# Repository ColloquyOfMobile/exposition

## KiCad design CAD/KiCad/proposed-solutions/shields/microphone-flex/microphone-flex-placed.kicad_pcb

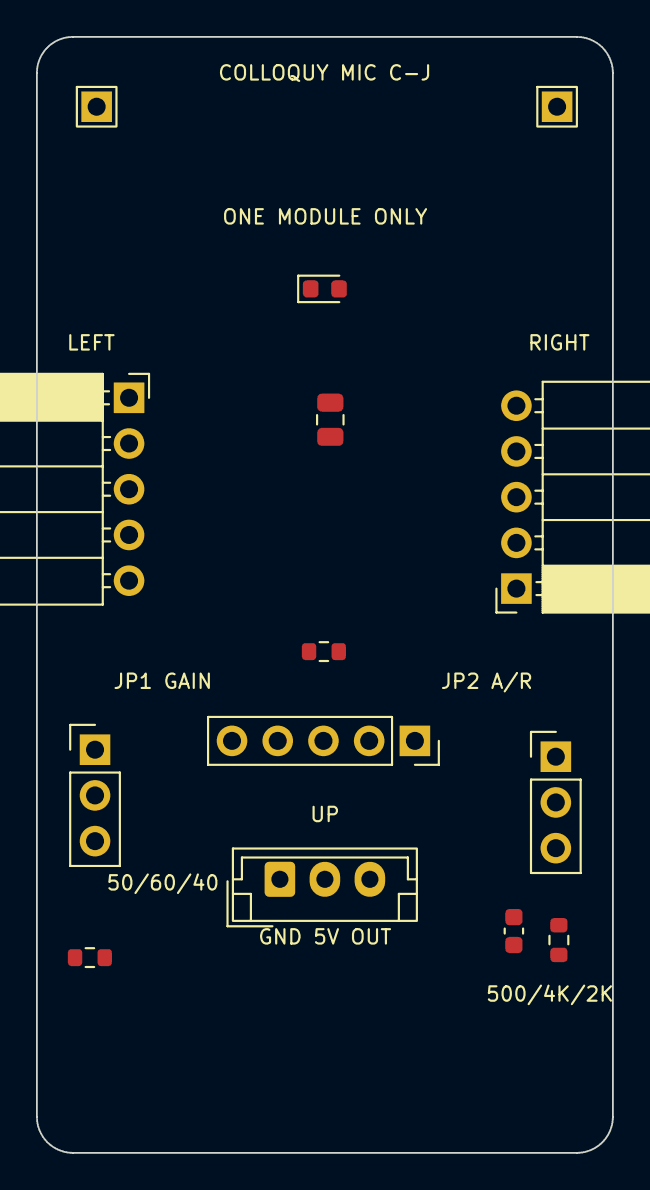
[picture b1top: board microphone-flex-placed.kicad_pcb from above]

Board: 2 copper layers, 32.0 x 62.0 mm, 16 parts (0 on the bottom side), 8 nets, no tracks yet.

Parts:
C6: 100nF; C_0603_1608Metric
C7: 22uF X5R 10V; C_0805_2012Metric
D1: GREEN LED; LED_0603_1608Metric
H1, H2: M5 SLOT 12x5.5 / TRANSVERSE; Flex_M5_Slot12x5.5_Keepout
J1: GND / +5V / OUT; JST_EH_B3B-EH-A_1x03_P2.50mm_Vertical
J2: LEFT / DOWNWARD MODULE; Flex_Socket_Side
J3: RIGHT / DOWNWARD MODULE; Flex_Socket_Side
JP1: GAIN SELECT / HEADER + SHUNT; Flex_Gain_Selector
JP2: AR SELECT / HEADER + SHUNT; Flex_AR_Selector
M1: UP / ONE MODULE ONLY; Flex_Socket_Up
R4: 33R; R_0603_1608Metric
R5: 470R; R_0603_1608Metric
R6: 2K2; R_0603_1608Metric
TP1: MICOUT; TestPin_1x01_P2.54mm
TP2: GND; TestPin_1x01_P2.54mm

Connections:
+5V: J1.2, R4.1, R6.1
AR: J2.5, J3.5, JP2.2, M1.5
GAIN: J2.3, J3.3, JP1.2, M1.3
GND: C6.2, C7.2, D1.1, J1.1, J2.1, J3.1, JP1.1, JP2.1, M1.1, TP2.1
MICOUT: J2.4, J3.4, M1.4, R5.1, TP1.1
OUT: J1.3, R5.2
VDD: C6.1, C7.1, J2.2, J3.2, JP1.3, JP2.3, M1.2, R4.2
led/D1: D1.2, R6.2

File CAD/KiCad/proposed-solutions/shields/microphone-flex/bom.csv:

Reference,Value,Footprint,MPN,Assembly
M1,UP / ONE MODULE ONLY,Shields:Flex_Socket_Up,Existing MAX9814 module + 1x05 2.54mm female socket,fit
R4,33R,Shields:R_0603_1608Metric,,fit
C7,22uF X5R 10V,Shields:C_0805_2012Metric,,fit
C6,100nF,Shields:C_0603_1608Metric,,fit
R6,2K2,Shields:R_0603_1608Metric,,fit
D1,GREEN LED,Shields:LED_0603_1608Metric,,fit
R5,470R,Shields:R_0603_1608Metric,,fit
J1,GND / +5V / OUT,Shields:JST_EH_B3B-EH-A_1x03_P2.50mm_Vertical,B3B-EH-A,fit
TP1,MICOUT,Shields:TestPin_1x01_P2.54mm,,fit
TP2,GND,Shields:TestPin_1x01_P2.54mm,,fit
JP1,GAIN SELECT / HEADER + SHUNT,Shields:Flex_Gain_Selector,Gold plated 1x03 2.54mm vertical header + removable 1x02 shunt,fit
JP2,AR SELECT / HEADER + SHUNT,Shields:Flex_AR_Selector,Gold plated 1x03 2.54mm vertical header + removable 1x02 shunt,fit
J2,LEFT / DOWNWARD MODULE,Shields:Flex_Socket_Left_Overhang,1x05 P2.54mm horizontal female socket; verify purchased dimensions,fit
J3,RIGHT / DOWNWARD MODULE,Shields:Flex_Socket_Right_Overhang,1x05 P2.54mm horizontal female socket; verify purchased dimensions,fit

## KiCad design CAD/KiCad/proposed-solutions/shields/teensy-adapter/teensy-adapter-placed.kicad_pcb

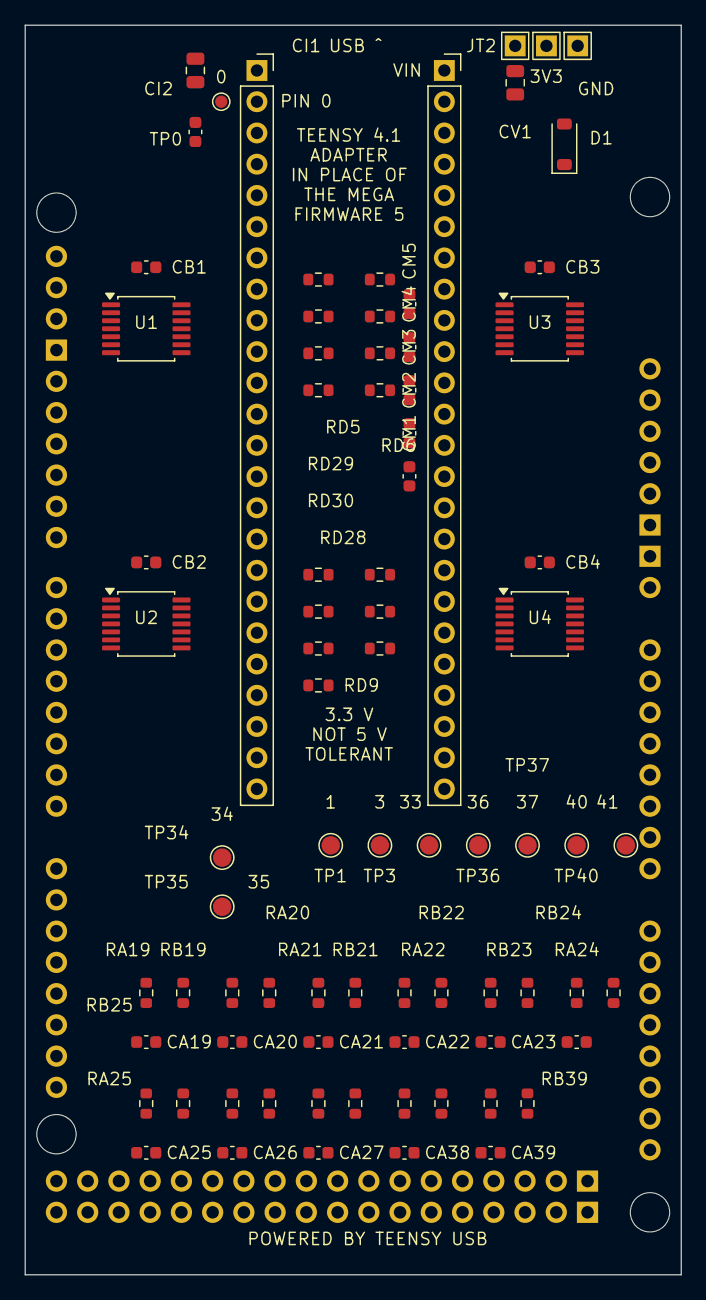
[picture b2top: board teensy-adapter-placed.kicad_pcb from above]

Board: 4 copper layers, 53.3 x 101.6 mm, 85 parts (1 on the bottom side), 71 nets, no tracks yet.

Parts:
CA19, CA20, CA21, CA22, CA23, CA24, CA25, CA26, CA27, CA38, CA39: 10nF C0G; C_0603_1608Metric
CB1, CB2, CB3, CB4: 100nF; C_0603_1608Metric
CI1: 10uF X7R; C_0805_2012Metric
CI2: 100nF; C_0603_1608Metric
CM1, CM2, CM3, CM4, CM5: 1nF C0G; C_0603_1608Metric
CV1: 10uF X7R; C_0805_2012Metric
D1: 1N5819HW; D_SOD-123
HM1, HM2, HM3, HM4: M3 computing shield; MountingHole_3.2mm_M3
JM1: MEGA PATTERN FEMALE; Mega_Female
JT1: Teensy 4.1 JT1; PinSocket_1x24_P2.54mm_Vertical
JT2: Teensy 4.1 JT2; PinSocket_1x24_P2.54mm_Vertical
RA19, RA20, RA21, RA22, RA23, RA24, RA25, RA26, RA27, RA38, RA39: 100K; R_0603_1608Metric
RB19, RB20, RB21, RB22, RB23, RB24, RB25, RB26, RB27, RB38, RB39: 150K; R_0603_1608Metric
RD2, RD4, RD5, RD6, RD7, RD8, RD9, RD10, RD11, RD12, RD28, RD29, RD30, RD31, RD32: 100K; R_0603_1608Metric
TP0: gpio/0; TestPoint_Pad_D1.0mm
TP1: gpio/1; TestPoint_Pad_D1.5mm
TP3: gpio/3; TestPoint_Pad_D1.5mm
TP33: gpio/33; TestPoint_Pad_D1.5mm
TP34: gpio/34; TestPoint_Pad_D1.5mm
TP35: gpio/35; TestPoint_Pad_D1.5mm
TP36: gpio/36; TestPoint_Pad_D1.5mm
TP37: gpio/37; TestPoint_Pad_D1.5mm
TP40: gpio/40; TestPoint_Pad_D1.5mm
TP41: gpio/41; TestPoint_Pad_D1.5mm
TPG: GND; TestPin_1x01_P2.54mm
TPI: IOREF; TestPin_1x01_P2.54mm
TPV: VIN_USB; TestPin_1x01_P2.54mm
U1, U2, U3, U4: SN74LV4T125PWR; TSSOP-14_4.4x5mm_P0.65mm

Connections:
GND: CA19.2, CA20.2, CA21.2, CA22.2, CA23.2, CA24.2, CA25.2, CA26.2, CA27.2, CA38.2, CA39.2, CB1.2, CB2.2, CB3.2, CB4.2, CI1.2, CI2.2, CM1.2, CM2.2, CM3.2, CM4.2, CM5.2, CV1.2, JM1.GND1, JM1.GND2, JM1.GND3, JM1.GND5, JM1.GND6, JT1.1, JT2.2, JT2.15, RB19.2, RB20.2, RB21.2, RB22.2, RB23.2, RB24.2, RB25.2, RB26.2, RB27.2, RB38.2, RB39.2, RD2.2, RD4.2, RD5.2, RD6.2, RD7.2, RD8.2, RD9.2, RD10.2, RD11.2, RD12.2, RD28.2, RD29.2, RD30.2, RD31.2, RD32.2, TPG.1, U1.1, U1.4, U1.7, U1.10, U1.13, U2.1, U2.4, U2.7, U2.10, U2.13, U3.1, U3.4, U3.7, U3.10, U3.13, U4.1, U4.4, U4.7, U4.10, U4.12, U4.13
IOREF: CI1.1, CI2.1, JT1.15, JT2.3, TPI.1
MEGA_5V: D1.1, JM1.5V1, JM1.5V3, JM1.5V4
VIN_USB: CB1.1, CB2.1, CB3.1, CB4.1, CV1.1, D1.2, JT2.1, TPV.1, U1.14, U2.14, U3.14, U4.14
adc/19: CA19.1, JT2.8, RA19.2, RB19.1
adc/20: CA20.1, JT2.7, RA20.2, RB20.1
adc/21: CA21.1, JT2.6, RA21.2, RB21.1
adc/22: CA22.1, JT2.5, RA22.2, RB22.1
adc/23: CA23.1, JT2.4, RA23.2, RB23.1
adc/24: CA24.1, JT1.16, RA24.2, RB24.1
adc/25: CA25.1, JT1.17, RA25.2, RB25.1
adc/26: CA26.1, JT1.18, RA26.2, RB26.1
adc/27: CA27.1, JT1.19, RA27.2, RB27.1
adc/38: CA38.1, JT2.19, RA38.2, RB38.1
adc/39: CA39.1, JT2.18, RA39.2, RB39.1
amp shutdown: JM1.D2, U4.8
female1/mic direct: CM1.1, JM1.D26, JT2.13
female1/neopixel/driven: JM1.D14, U2.6
female1/photosensor: JM1.A5, RA19.1
female1/tone: JM1.D6, U1.3
female2/mic direct: CM2.1, JM1.D27, JT2.12
female2/neopixel/driven: JM1.D7, U2.8
female2/photosensor: JM1.A6, RA20.1
female2/tone: JM1.D46, U1.6
female3/mic direct: CM3.1, JM1.D28, JT2.11
female3/neopixel/driven: JM1.D8, U2.11
female3/photosensor: JM1.A7, RA21.1
female3/tone: JM1.D10, U1.8
gpio/0: JT1.2, TP0.1
gpio/1: JT1.3, TP1.1
gpio/2: JT1.4, RD2.1, U1.2
gpio/3: JT1.5, TP3.1
gpio/4: JT1.6, RD4.1, U1.5
gpio/5: JT1.7, RD5.1, U1.9
gpio/6: JT1.8, RD6.1, U1.12
gpio/7: JT1.9, RD7.1, U2.5
gpio/8: JT1.10, RD8.1, U2.9
gpio/9: JT1.11, RD9.1, U2.12
gpio/10: JT1.12, RD10.1, U3.2
gpio/11: JT1.13, RD11.1, U3.5
gpio/12: JT1.14, RD12.1, U3.9
gpio/28: JT1.20, RD28.1, U2.2
gpio/29: JT1.21, RD29.1, U3.12
gpio/30: JT1.22, RD30.1, U4.2
gpio/31: JT1.23, RD31.1, U4.5
gpio/32: JT1.24, RD32.1, U4.9
gpio/33: JT2.24, TP33.1
gpio/34: JT2.23, TP34.1
gpio/35: JT2.22, TP35.1
gpio/36: JT2.21, TP36.1
gpio/37: JT2.20, TP37.1
gpio/40: JT2.17, TP40.1
gpio/41: JT2.16, TP41.1
male1/aux driven: JM1.D24, U4.3
male1/bar neopixel/driven: JM1.D16, U3.11
male1/mic direct: CM4.1, JM1.D29, JT2.10
male1/neopixel/driven: JM1.D9, U3.3
male1/photosensor/A: JM1.A8, RA22.1
male1/photosensor/B: JM1.A9, RA23.1
male1/photosensor/C: JM1.A10, RA24.1
male1/photosensor/D: JM1.A11, RA25.1
male1/tone: JM1.D11, U1.11
male2/aux driven: JM1.D25, U4.6
male2/bar neopixel/driven: JM1.D17, U3.8
male2/mic direct: CM5.1, JM1.D30, JT2.9
male2/neopixel/driven: JM1.D15, U3.6
male2/photosensor/A: JM1.A12, RA26.1
male2/photosensor/B: JM1.A13, RA27.1
male2/photosensor/C: JM1.A14, RA38.1
male2/photosensor/D: JM1.A15, RA39.1
male2/tone: JM1.D5, U2.3

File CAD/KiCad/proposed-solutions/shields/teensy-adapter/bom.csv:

Reference,Value,Footprint,MPN,Assembly
JM1,MEGA PATTERN FEMALE,Shields:Mega_Female,,fit
CM1,1nF C0G,Shields:C_0603_1608Metric,,fit
CM2,1nF C0G,Shields:C_0603_1608Metric,,fit
CM3,1nF C0G,Shields:C_0603_1608Metric,,fit
CM4,1nF C0G,Shields:C_0603_1608Metric,,fit
CM5,1nF C0G,Shields:C_0603_1608Metric,,fit
JT1,Teensy 4.1 JT1,Shields:PinSocket_1x24_P2.54mm_Vertical,,fit
JT2,Teensy 4.1 JT2,Shields:PinSocket_1x24_P2.54mm_Vertical,,fit
RD2,100K,Shields:R_0603_1608Metric,,fit
RD4,100K,Shields:R_0603_1608Metric,,fit
RD5,100K,Shields:R_0603_1608Metric,,fit
RD6,100K,Shields:R_0603_1608Metric,,fit
U1,SN74LV4T125PWR,Shields:TSSOP-14_4.4x5mm_P0.65mm,SN74LV4T125PWR,fit
CB1,100nF,Shields:C_0603_1608Metric,,fit
RD28,100K,Shields:R_0603_1608Metric,,fit
RD7,100K,Shields:R_0603_1608Metric,,fit
RD8,100K,Shields:R_0603_1608Metric,,fit
RD9,100K,Shields:R_0603_1608Metric,,fit
U2,SN74LV4T125PWR,Shields:TSSOP-14_4.4x5mm_P0.65mm,SN74LV4T125PWR,fit
CB2,100nF,Shields:C_0603_1608Metric,,fit
RD10,100K,Shields:R_0603_1608Metric,,fit
RD11,100K,Shields:R_0603_1608Metric,,fit
RD12,100K,Shields:R_0603_1608Metric,,fit
RD29,100K,Shields:R_0603_1608Metric,,fit
U3,SN74LV4T125PWR,Shields:TSSOP-14_4.4x5mm_P0.65mm,SN74LV4T125PWR,fit
CB3,100nF,Shields:C_0603_1608Metric,,fit
RD30,100K,Shields:R_0603_1608Metric,,fit
RD31,100K,Shields:R_0603_1608Metric,,fit
RD32,100K,Shields:R_0603_1608Metric,,fit
U4,SN74LV4T125PWR,Shields:TSSOP-14_4.4x5mm_P0.65mm,SN74LV4T125PWR,fit
CB4,100nF,Shields:C_0603_1608Metric,,fit
RA19,100K,Shields:R_0603_1608Metric,,fit
RB19,150K,Shields:R_0603_1608Metric,,fit
CA19,10nF C0G,Shields:C_0603_1608Metric,,fit
RA20,100K,Shields:R_0603_1608Metric,,fit
RB20,150K,Shields:R_0603_1608Metric,,fit
CA20,10nF C0G,Shields:C_0603_1608Metric,,fit
RA21,100K,Shields:R_0603_1608Metric,,fit
RB21,150K,Shields:R_0603_1608Metric,,fit
CA21,10nF C0G,Shields:C_0603_1608Metric,,fit
RA22,100K,Shields:R_0603_1608Metric,,fit
RB22,150K,Shields:R_0603_1608Metric,,fit
CA22,10nF C0G,Shields:C_0603_1608Metric,,fit
RA23,100K,Shields:R_0603_1608Metric,,fit
RB23,150K,Shields:R_0603_1608Metric,,fit
CA23,10nF C0G,Shields:C_0603_1608Metric,,fit
RA24,100K,Shields:R_0603_1608Metric,,fit
RB24,150K,Shields:R_0603_1608Metric,,fit
CA24,10nF C0G,Shields:C_0603_1608Metric,,fit
RA25,100K,Shields:R_0603_1608Metric,,fit
RB25,150K,Shields:R_0603_1608Metric,,fit
CA25,10nF C0G,Shields:C_0603_1608Metric,,fit
RA26,100K,Shields:R_0603_1608Metric,,fit
RB26,150K,Shields:R_0603_1608Metric,,fit
CA26,10nF C0G,Shields:C_0603_1608Metric,,fit
RA27,100K,Shields:R_0603_1608Metric,,fit
RB27,150K,Shields:R_0603_1608Metric,,fit
CA27,10nF C0G,Shields:C_0603_1608Metric,,fit
RA38,100K,Shields:R_0603_1608Metric,,fit
RB38,150K,Shields:R_0603_1608Metric,,fit
CA38,10nF C0G,Shields:C_0603_1608Metric,,fit
RA39,100K,Shields:R_0603_1608Metric,,fit
RB39,150K,Shields:R_0603_1608Metric,,fit
CA39,10nF C0G,Shields:C_0603_1608Metric,,fit
D1,1N5819HW,Shields:D_SOD-123,1N5819HW,fit
CV1,10uF X7R,Shields:C_0805_2012Metric,,fit
CI1,10uF X7R,Shields:C_0805_2012Metric,,fit
CI2,100nF,Shields:C_0603_1608Metric,,fit
TPV,VIN_USB,Shields:TestPin_1x01_P2.54mm,,fit
TPI,IOREF,Shields:TestPin_1x01_P2.54mm,,fit
TPG,GND,Shields:TestPin_1x01_P2.54mm,,fit

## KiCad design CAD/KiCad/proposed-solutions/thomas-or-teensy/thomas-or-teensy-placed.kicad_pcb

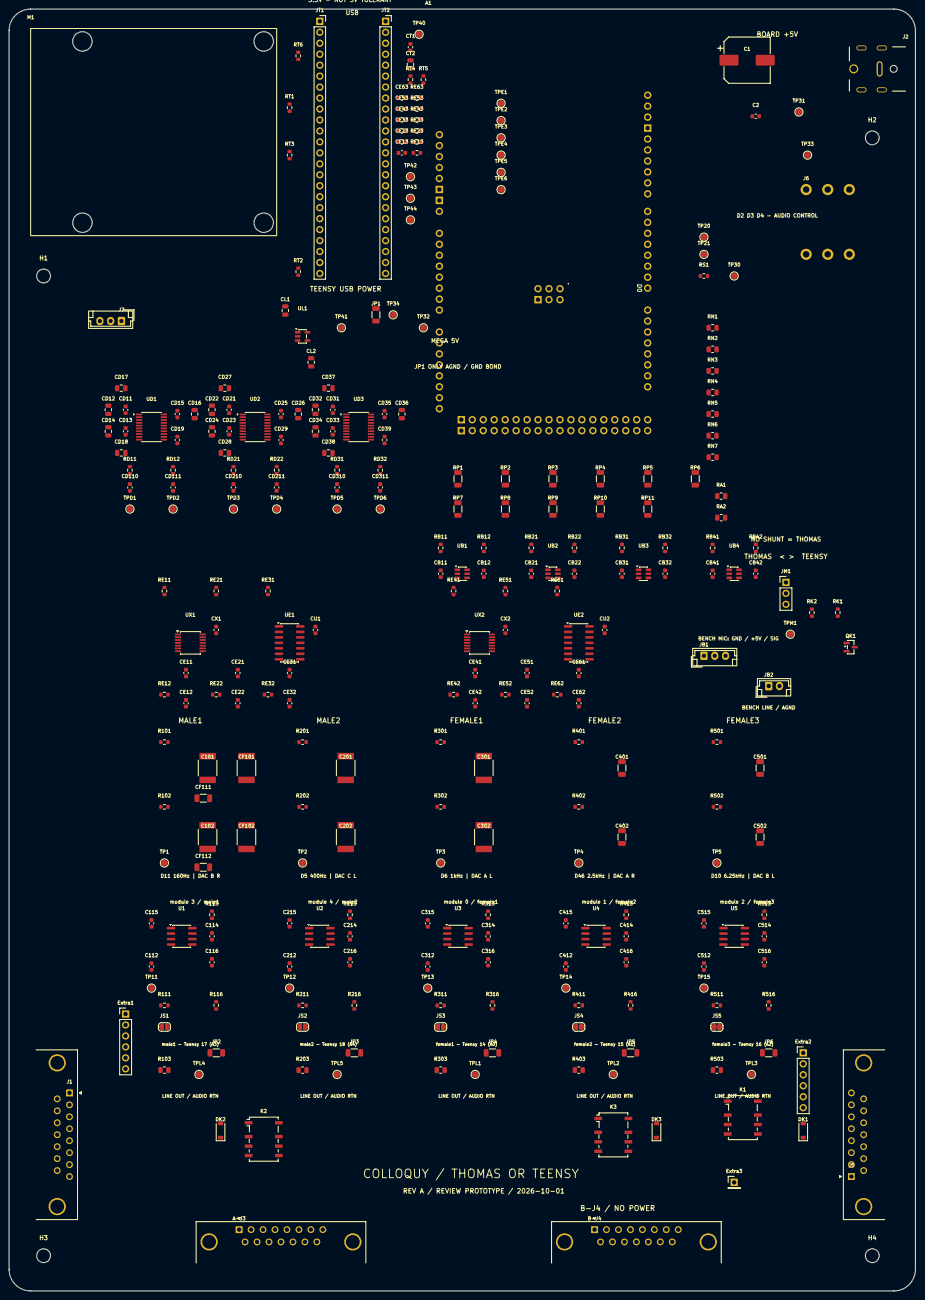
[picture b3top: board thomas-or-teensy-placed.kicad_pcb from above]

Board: 2 copper layers, 210.0 x 297.0 mm, 290 parts (0 on the bottom side), 192 nets, no tracks yet.

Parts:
A1: Arduino Mega 2560; Arduino_Mega2560_R3_Shield
A-J3: DSUB-15; DSUB-15_Pins_Horizontal_P2.77x2.84mm_EdgePinOffset4.94mm_Ho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
B-J4: DSUB-15; DSUB-15_Pins_Horizontal_P2.77x2.84mm_EdgePinOffset4.94mm_Ho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
C1: 470uF 25V; CP_Elec_10x10.5
C2, C112, C115, C116, C212, C215, C216, C312, C315, C316, C412, C415, C416, C512, C515, C516: 100nF; C_0603_1608Metric
C101, C102, C201, C202: 220nF PPS 5%; PPS_6041
C114, C214, C314, C414, C514: 33pF C0G; C_0603_1608Metric
C301, C302: 150nF PPS 5%; PPS_6041
C401, C402: 47nF C0G 5%; C_1206_3216Metric
C501, C502: 10nF C0G 5%; C_1206_3216Metric
CB11, CB12, CB21, CB22, CB31, CB32, CB41, CB42: 100nF; C_0603_1608Metric
CD11, CD13, CD15, CD19, CD21, CD23, CD25, CD29, CD31, CD33, CD35, CD39: 100nF; C_0603_1608Metric
CD12, CD14, CD16, CD22, CD24, CD26, CD32, CD34, CD36: 10uF; C_0805_2012Metric
CD17, CD18, CD27, CD28, CD37, CD38: 2.2uF; C_0805_2012Metric
CD110, CD111, CD210, CD211, CD310, CD311: 2.2nF C0G; C_0603_1608Metric
CE11, CE21, CE31, CE41, CE51, CE61: 2.2nF C0G; C_0603_1608Metric
CE12, CE13, CE22, CE23, CE32, CE33, CE42, CE43, CE52, CE53, CE62, CE63: 1nF C0G; C_0603_1608Metric
CF101, CF102: 220nF PPS 5%; PPS_6041
CF111, CF112: 30nF C0G 5%; C_1206_3216Metric
CL1, CL2: 10uF; C_0805_2012Metric
CT1: 100nF; C_0603_1608Metric
CT2: 10uF; C_0805_2012Metric
CU1, CU2: 100nF; C_0603_1608Metric
CX1, CX2: 100nF; C_0603_1608Metric
DK1, DK2, DK3: 1N4148W; D_SOD-123
Extra1, Extra2: 1x6 header; PinHeader_1x06_P2.54mm_Vertical
Extra3: 1x1 pad; PinHeader_1x01_P2.54mm_Vertical
H1, H2, H3, H4: M3 3.2mm NPTH; MountingHole_3.2mm_M3
J1, J5: DSUB-15; DSUB-15_Pins_Horizontal_P2.77x2.84mm_EdgePinOffset4.94mm_Ho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
J2: DC jack; PJ-082BH_jack_10A
J6: screw bridge; screw_brigde
J7: JST EH 3; JST_EH_B3B-EH-A_1x03_P2.50mm_Vertical
JB1: BENCH MIC GND +5V SIGNAL; JST_EH_B3B-EH-A_1x03_P2.50mm_Vertical
JB2: BENCH LINE / AGND; JST_EH_B2B-EH-A_1x02_P2.50mm_Vertical
JM1: THOMAS / MODE / TEENSY; PinHeader_1x03_P2.54mm_Vertical
JP1, JP2, JP3, JP4, JP5, JP6: 0R; R_1206_3216Metric
JS1, JS2, JS3, JS4, JS5: ATTEN BYPASS (OPEN); SolderJumper-2_P1.3mm_Open_RoundedPad1.0x1.5mm
JT1: Teensy 4.1 LEFT; PinSocket_1x24_P2.54mm_Vertical
JT2: Teensy 4.1 RIGHT; PinSocket_1x24_P2.54mm_Vertical
K1, K2, K3: G6K-2F-Y DC5; Relay_DPDT_Omron_G6K-2F-Y
M1: U2D2; u2d2_mounting
QK1: 2N7002; SOT-23
R101, R102, R501, R502: 2K2; R_0603_1608Metric
R103, R203, R303, R403, R503: 100R; R_0805_2012Metric
R111, R211, R311, R411, R511: 47K; R_0603_1608Metric
R113, R213, R313, R413, R513: 200K 1%; R_0603_1608Metric
R116, R216, R316, R416, R516: 6K8; R_0603_1608Metric
R201, R202: 2K; R_0603_1608Metric
R301, R302: 1K2; R_0603_1608Metric
R401, R402: 1K8; R_0603_1608Metric
RA1, RA2: 330R; R_0805_2012Metric
RB11, RB12, RB21, RB22, RB31, RB32, RB41, RB42: 100K; R_0603_1608Metric
RD11, RD12, RD21, RD22, RD31, RD32: 470R; R_0603_1608Metric
RE11, RE12, RE21, RE22, RE31, RE32, RE41, RE42, RE51, RE52, RE61, RE62: 10K 1%; R_0603_1608Metric
RE13, RE23, RE33, RE43, RE53, RE63: 100R; R_0603_1608Metric
RK1: 100R; R_0603_1608Metric
RK2: 100K; R_0603_1608Metric
RN1, RN2, RN3, RN4, RN5, RN6, RN7: 330R; R_0805_2012Metric
RP1, RP2, RP3, RP4, RP5, RP6, RP7, RP8, RP9, RP10, RP11: 10K provisional; R_1206_3216Metric
RS1: 10K; R_0603_1608Metric
RT1, RT2, RT3, RT4, RT5: 33R; R_0603_1608Metric
RT6: 10K; R_0603_1608Metric
TP1, TP2, TP3, TP4, TP5, TP11, TP12, TP13, TP14, TP15, TP20, TP21, TP30, TP31, TP32, TP33, TP34: test pad; TestPoint_Pad_D1.5mm
TP40: TEENSY_3V3; TestPoint_Pad_D1.5mm
TP41: DAC_3V3; TestPoint_Pad_D1.5mm
TP42: TEENSY_A8; TestPoint_Pad_D1.5mm
TP43: BCLK; TestPoint_Pad_D1.5mm
TP44: LRCLK; TestPoint_Pad_D1.5mm
TPD1: female1/dac; TestPoint_Pad_D1.5mm
TPD2: female2/dac; TestPoint_Pad_D1.5mm
TPD3: female3/dac; TestPoint_Pad_D1.5mm
TPD4: male1/dac; TestPoint_Pad_D1.5mm
TPD5: male2/dac; TestPoint_Pad_D1.5mm
TPD6: bench/dac; TestPoint_Pad_D1.5mm
TPE1: female1/adc; TestPoint_Pad_D1.5mm
TPE2: female2/adc; TestPoint_Pad_D1.5mm
TPE3: female3/adc; TestPoint_Pad_D1.5mm
TPE4: male1/adc; TestPoint_Pad_D1.5mm
TPE5: male2/adc; TestPoint_Pad_D1.5mm
TPE6: bench/adc; TestPoint_Pad_D1.5mm
TPL1: female1/selected; TestPoint_Pad_D1.5mm
TPL2: female2/selected; TestPoint_Pad_D1.5mm
TPL3: female3/selected; TestPoint_Pad_D1.5mm
TPL4: male1/selected; TestPoint_Pad_D1.5mm
TPL5: male2/selected; TestPoint_Pad_D1.5mm
TPM1: MODE; TestPoint_Pad_D1.5mm
U1, U2, U3, U4, U5: MSGEQ7N; SOIC-8_3.9x4.9mm_P1.27mm
UB1, UB2, UB3, UB4: SN74LVC1T45DBVR; SOT-23-6
UD1, UD2, UD3: PCM5102APWR; TSSOP-20_4.4x6.5mm_P0.65mm
UE1, UE2: MCP6004-I/SL; SOIC-14_3.9x8.7mm_P1.27mm
UL1: TLV75533PDBVR; SOT-23-5
UX1, UX2: TMUX1511PWR; TSSOP-14_4.4x5mm_P0.65mm

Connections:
+5V: A-J3.9, C1.1, C2.1, CB11.1, CB21.1, DK1.1, DK2.1, DK3.1, J1.15, J2.1, J5.15, J6.3, J6.5, J6.6, JB1.2, JM1.3, K1.1, K2.1, K3.1, TP31.1, UB1.1, UB1.5, UB2.1, UB2.5
+12V: A-J3.2, J1.7, J5.7, J7.2
AGND: C101.2, C102.2, C114.2, C115.2, C116.2, C201.2, C202.2, C214.2, C215.2, C216.2, C301.2, C302.2, C314.2, C315.2, C316.2, C401.2, C402.2, C414.2, C415.2, C416.2, C501.2, C502.2, C514.2, C515.2, C516.2, CD11.2, CD12.2, CD13.2, CD14.2, CD15.2, CD16.2, CD18.2, CD19.2, CD21.2, CD22.2, CD23.2, CD24.2, CD25.2, CD26.2, CD28.2, CD29.2, CD31.2, CD32.2, CD33.2, CD34.2, CD35.2, CD36.2, CD38.2, CD39.2, CD110.2, CD111.2, CD210.2, CD211.2, CD310.2, CD311.2, CE12.2, CE13.2, CE22.2, CE23.2, CE32.2, CE33.2, CE42.2, CE43.2, CE52.2, CE53.2, CE62.2, CE63.2, CF101.2, CF102.2, CF111.2, CF112.2, CL1.2, CL2.2, CU1.2, CU2.2, CX1.2, CX2.2, JB1.1, JB2.2, JP1.1, JP2.2, JP3.2, JP4.2, JP5.2, JP6.2, R116.2, R216.2, R316.2, R416.2, R516.2, RP1.2, RP2.2, RP3.2, RP4.2, RP5.2, RP6.2, RP7.2, RP8.2, RP9.2, RP10.2, RP11.2, TP34.1, U1.2, U2.2, U3.2, U4.2, U5.2, UD1.3, UD1.9, UD1.10, UD1.11, UD1.12, UD1.16, UD1.19, UD2.3, UD2.9, UD2.10, UD2.11, UD2.12, UD2.16, UD2.19, UD3.3, UD3.9, UD3.10, UD3.11, UD3.12, UD3.16, UD3.19, UE1.11, UE1.12, UE2.11, UE2.12, UL1.2, UX1.7, UX1.12, UX1.13, UX2.7, UX2.12, UX2.13
BCLK: RT5.2, TP43.1, UD1.13, UD2.13, UD3.13
BCLK_raw: JT2.6, RT5.1
COIL_GATE: QK1.1, RK1.2
COIL_LOW: DK1.2, DK2.2, DK3.2, K1.8, K2.8, K3.8, QK1.3
DAC_3V3: CD11.1, CD12.1, CD13.1, CD14.1, CD15.1, CD16.1, CD21.1, CD22.1, CD23.1, CD24.1, CD25.1, CD26.1, CD31.1, CD32.1, CD33.1, CD34.1, CD35.1, CD36.1, CL2.1, TP41.1, UD1.1, UD1.8, UD1.20, UD2.1, UD2.8, UD2.20, UD3.1, UD3.8, UD3.20, UL1.5
DAC_A/CAPM: CD17.2, UD1.4
DAC_A/CAPP: CD17.1, UD1.2
DAC_A/LDOO: CD19.1, UD1.18
DAC_A/VNEG: CD18.1, UD1.5
DAC_B/CAPM: CD27.2, UD2.4
DAC_B/CAPP: CD27.1, UD2.2
DAC_B/LDOO: CD29.1, UD2.18
DAC_B/VNEG: CD28.1, UD2.5
DAC_C/CAPM: CD37.2, UD3.4
DAC_C/CAPP: CD37.1, UD3.2
DAC_C/LDOO: CD39.1, UD3.18
DAC_C/VNEG: CD38.1, UD3.5
DAC_XSMT: JT1.4, RT6.1, UD1.17, UD2.17, UD3.17
GND: A1.GND1, A1.GND2, A1.GND3, A1.GND4, A1.GND5, A1.GND6, A-J3.0, A-J3.1, B-J4.0, C1.2, C2.2, CB11.2, CB12.2, CB21.2, CB22.2, CB31.2, CB32.2, CB41.2, CB42.2, CT1.2, CT2.2, J1.0, J1.8, J2.2, J5.0, J5.8, J6.1, J6.2, J6.4, J7.1, JM1.1, JP1.2, JT1.1, JT2.2, JT2.15, QK1.2, RB11.2, RB12.2, RB21.2, RB22.2, RB31.2, RB32.2, RB41.2, RB42.2, RK2.2, RT6.2, TP33.1, UB1.2, UB2.2, UB3.2, UB4.2
I2S_A: RT1.2, UD1.14
I2S_A_raw: JT1.9, RT1.1
I2S_B: RT2.2, UD2.14
I2S_B_raw: JT1.24, RT2.1
I2S_C: RT3.2, UD3.14
I2S_C_raw: JT1.11, RT3.1
LRCLK: RT4.2, TP44.1, UD1.15, UD2.15, UD3.15
LRCLK_raw: JT2.7, RT4.1
MEGA_5V: A1.5V1, A1.5V2, A1.5V3, A1.5V4, C115.1, C215.1, C315.1, C415.1, C515.1, CB12.1, CB31.1, CB42.1, R113.1, R213.1, R313.1, R413.1, R513.1, RS1.2, TP32.1, U1.1, U2.1, U3.1, U4.1, U5.1, UB1.6, UB3.1, UB3.5, UB4.6
MODE: JM1.2, RB11.1, RB21.1, RK1.1, RK2.1, TPM1.1, UB1.3, UB2.3
MODE_MEGA: A1.D30, RB12.1, UB1.4
MODE_TEENSY: JT1.5, RB22.1, UB2.4
TEENSY_3V3: CB22.1, CB32.1, CB41.1, CT1.1, CT2.1, CU1.1, CU2.1, CX1.1, CX2.1, JT1.15, JT2.3, TP40.1, UB2.6, UB3.6, UB4.1, UB4.5, UE1.4, UE2.4, UX1.1, UX1.4, UX1.10, UX1.14, UX2.1, UX2.4, UX2.10, UX2.14
TEENSY_A8: JT2.5, TP42.1
TEENSY_VIN: CL1.1, JT2.1, UL1.1, UL1.3
amp shutdown: A1.D2, RS1.1, TP30.1
analyser/reset: A1.D3, TP21.1, U1.7, U2.7, U3.7, U4.7, U5.7
analyser/strobe: A1.D4, TP20.1, U1.4, U2.4, U3.4, U4.4, U5.4
bench/adc: CE63.1, JT2.8, RE63.2, TPE6.1
bench/buffer: CE61.2, RE63.1, UE2.8, UE2.9
bench/dac: CD311.1, JB2.1, RD32.2, TPD6.1
bench/dac raw: RD32.1, UD3.7
bench/filter: CE62.1, RE62.2, UE2.10
bench/isolator in: RE61.2, UX2.9
bench/microphone: JB1.3, RE61.1
bench/mid: CE61.1, RE62.1, UX2.8
centre/spare1: B-J4.7, Extra3.1
dxl_data: A-J3.10, J1.14, J5.14, J7.3
female1/adc: CE13.1, JT2.13, RE13.2, TPE1.1
female1/analyser out: A1.A0, TP13.1, U3.3
female1/audio return: J5.4, JP4.1
female1/buffer: CE11.2, RE13.1, UE1.1, UE1.2
female1/dac: CD110.1, K1.4, RD11.2, TPD1.1
female1/dac raw: RD11.1, UD1.6
female1/filter: CE12.1, RE12.2, UE1.3
female1/filter mid: C301.1, R301.2, R302.1
female1/filter out: C302.1, K1.2, R302.2, TP3.1
female1/internal reference: C316.1, U3.6
female1/isolator in: RE11.2, UX1.2
female1/line out: J5.12, R303.2
female1/mic attenuated: C312.1, JS3.2, R311.2, R316.1
female1/microphone: J5.6, JS3.1, R311.1, RE11.1
female1/mid: CE11.1, RE12.1, UX1.3
female1/msgeq input: C312.2, U3.5
female1/neopixel: J5.13, RN1.2
female1/neopixel/driven: A1.D14, RN1.1
female1/oscillator: C314.1, R313.2, U3.8
female1/photosensor: A1.A5, J5.5, RP1.1
female1/selected: K1.3, R303.1, TPL1.1
female1/spare1: Extra2.1, J5.1
female1/spare2: Extra2.2, J5.2
female1/spare3: Extra2.3, J5.3
female1/spare4: Extra2.4, J5.9
female1/spare5: Extra2.5, J5.10
female1/spare6: Extra2.6, J5.11
female1/tone: A1.D6, R301.1
female2/adc: CE23.1, JT2.12, RE23.2, TPE2.1
female2/analyser out: A1.A1, TP14.1, U4.3
female2/audio return: J1.4, JP5.1
female2/buffer: CE21.2, RE23.1, UE1.6, UE1.7
female2/dac: CD111.1, K1.5, RD12.2, TPD2.1
female2/dac raw: RD12.1, UD1.7
female2/filter: CE22.1, RE22.2, UE1.5
female2/filter mid: C401.1, R401.2, R402.1
female2/filter out: C402.1, K1.7, R402.2, TP4.1
female2/internal reference: C416.1, U4.6
female2/isolator in: RE21.2, UX1.5
female2/line out: J1.12, R403.2
female2/mic attenuated: C412.1, JS4.2, R411.2, R416.1
female2/microphone: J1.6, JS4.1, R411.1, RE21.1
female2/mid: CE21.1, RE22.1, UX1.6
female2/msgeq input: C412.2, U4.5
female2/neopixel: J1.13, RN2.2
female2/neopixel/driven: A1.D7, RN2.1
female2/oscillator: C414.1, R413.2, U4.8
female2/photosensor: A1.A6, J1.5, RP2.1
female2/selected: K1.6, R403.1, TPL2.1
female2/spare1: Extra1.1, J1.1
female2/spare2: Extra1.2, J1.2
female2/spare3: Extra1.3, J1.3
female2/spare4: Extra1.4, J1.9
female2/spare5: Extra1.5, J1.10
female2/spare6: Extra1.6, J1.11
female2/tone: A1.D46, R401.1
female3/adc: CE33.1, JT2.11, RE33.2, TPE3.1
female3/analyser out: A1.A2, TP15.1, U5.3
female3/audio return: A-J3.5, JP6.1
female3/buffer: CE31.2, RE33.1, UE1.8, UE1.9
female3/dac: CD210.1, K2.4, RD21.2, TPD3.1
female3/dac raw: RD21.1, UD2.6
female3/filter: CE32.1, RE32.2, UE1.10
female3/filter mid: C501.1, R501.2, R502.1
female3/filter out: C502.1, K2.2, R502.2, TP5.1
female3/internal reference: C516.1, U5.6
female3/isolator in: RE31.2, UX1.9
female3/line out: A-J3.12, R503.2
female3/mic attenuated: C512.1, JS5.2, R511.2, R516.1
female3/microphone: A-J3.3, JS5.1, R511.1, RE31.1
female3/mid: CE31.1, RE32.1, UX1.8
female3/msgeq input: C512.2, U5.5
female3/neopixel: A-J3.11, RN3.2
female3/neopixel/driven: A1.D8, RN3.1
female3/oscillator: C514.1, R513.2, U5.8
female3/photosensor: A1.A7, A-J3.4, RP3.1
female3/selected: K2.3, R503.1, TPL3.1
female3/tone: A1.D10, R501.1
link/mega_tx: A1.D18, RB31.1, UB3.3
link/teensy_tx: JT1.3, RB41.1, UB4.3
link/to_mega: A1.D19, RB42.1, UB4.4
link/to_teensy: JT1.2, RB32.1, UB3.4
male1/adc: CE43.1, JT2.10, RE43.2, TPE4.1
male1/analyser out: A1.A3, TP11.1, U1.3
male1/audio return: B-J4.2, JP2.1
male1/aux: B-J4.1, RA1.2
male1/aux driven: A1.D24, RA1.1
male1/bar neopixel: B-J4.15, RN6.2
male1/bar neopixel/driven: A1.D16, RN6.1
male1/buffer: CE41.2, RE43.1, UE2.1, UE2.2
male1/dac: CD211.1, K2.5, RD22.2, TPD4.1
male1/dac raw: RD22.1, UD2.7
male1/filter: CE42.1, RE42.2, UE2.3
male1/filter mid: C101.1, CF101.1, CF111.1, R101.2, R102.1
male1/filter out: C102.1, CF102.1, CF112.1, K2.7, R102.2, TP1.1
male1/internal reference: C116.1, U1.6
male1/isolator in: RE41.2, UX2.2
male1/line out: B-J4.9, R103.2
male1/mic attenuated: C112.1, JS1.2, R111.2, R116.1
male1/microphone: A-J3.13, JS1.1, R111.1, RE41.1
male1/mid: CE41.1, RE42.1, UX2.3
male1/msgeq input: C112.2, U1.5
male1/neopixel: A-J3.6, RN4.2
male1/neopixel/driven: A1.D9, RN4.1
male1/oscillator: C114.1, R113.2, U1.8
male1/photosensor/A: A1.A8, A-J3.14, RP4.1
male1/photosensor/B: A1.A9, A-J3.7, RP5.1
male1/photosensor/C: A1.A10, A-J3.15, RP6.1
male1/photosensor/D: A1.A11, A-J3.8, RP7.1
male1/selected: K2.6, R103.1, TPL4.1
male1/tone: A1.D11, R101.1
male2/adc: CE53.1, JT2.9, RE53.2, TPE5.1
male2/analyser out: A1.A4, TP12.1, U2.3
male2/audio return: B-J4.14, JP3.1
male2/aux: B-J4.13, RA2.2
male2/aux driven: A1.D25, RA2.1
male2/bar neopixel: B-J4.8, RN7.2
male2/bar neopixel/driven: A1.D17, RN7.1
male2/buffer: CE51.2, RE53.1, UE2.6, UE2.7
male2/dac: CD310.1, K3.4, RD31.2, TPD5.1
male2/dac raw: RD31.1, UD3.6
male2/filter: CE52.1, RE52.2, UE2.5
male2/filter mid: C201.1, R201.2, R202.1
male2/filter out: C202.1, K3.2, R202.2, TP2.1
male2/internal reference: C216.1, U2.6
male2/isolator in: RE51.2, UX2.5
male2/line out: B-J4.6, R203.2
male2/mic attenuated: C212.1, JS2.2, R211.2, R216.1
male2/microphone: B-J4.10, JS2.1, R211.1, RE51.1
male2/mid: CE51.1, RE52.1, UX2.6
male2/msgeq input: C212.2, U2.5
male2/neopixel: B-J4.3, RN5.2
male2/neopixel/driven: A1.D15, RN5.1
male2/oscillator: C214.1, R213.2, U2.8
male2/photosensor/A: A1.A12, B-J4.11, RP8.1
male2/photosensor/B: A1.A13, B-J4.4, RP9.1
male2/photosensor/C: A1.A14, B-J4.12, RP10.1
male2/photosensor/D: A1.A15, B-J4.5, RP11.1
male2/selected: K3.3, R203.1, TPL5.1
male2/tone: A1.D5, R201.1
spare1/buffer: UE1.13, UE1.14
spare2/buffer: UE2.13, UE2.14

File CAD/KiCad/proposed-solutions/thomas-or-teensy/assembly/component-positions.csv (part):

Ref,Val,Package,PosX,PosY,Rot,Side
"A-J3","DSUB-15","DSUB-15_Pins_Horizontal_P2.77x2.84mm_EdgePinOffset4.94mm_Housed_MountingHolesOffset4.94mm",97.305000,-334.960000,0.000000,top
"A1","Arduino Mega 2560","Arduino_Mega2560_R3_Shield",141.160000,-53.320000,-90.000000,top
"B-J4","DSUB-15","DSUB-15_Pins_Horizontal_P2.77x2.84mm_EdgePinOffset4.94mm_Housed_MountingHolesOffset4.94mm",179.655000,-334.960000,0.000000,top
"C1","470uF 25V","CP_Elec_10x10.5",215.000000,-64.000000,0.000000,top
"C2","100nF","C_0603_1608Metric",217.000000,-77.000000,0.000000,top
"C101","220nF PPS 5%","PPS_6041",90.000000,-228.000000,90.000000,top
"C102","220nF PPS 5%","PPS_6041",90.000000,-244.000000,90.000000,top
"C112","100nF","C_0603_1608Metric",77.000000,-274.000000,90.000000,top
"C114","33pF C0G","C_0603_1608Metric",91.000000,-267.000000,90.000000,top
"C115","100nF","C_0603_1608Metric",77.000000,-264.000000,90.000000,top
"C116","100nF","C_0603_1608Metric",91.000000,-273.000000,90.000000,top
"C201","220nF PPS 5%","PPS_6041",122.000000,-228.000000,90.000000,top
"C202","220nF PPS 5%","PPS_6041",122.000000,-244.000000,90.000000,top
"C212","100nF","C_0603_1608Metric",109.000000,-274.000000,90.000000,top
"C214","33pF C0G","C_0603_1608Metric",123.000000,-267.000000,90.000000,top
"C215","100nF","C_0603_1608Metric",109.000000,-264.000000,90.000000,top
"C216","100nF","C_0603_1608Metric",123.000000,-273.000000,90.000000,top
"C301","150nF PPS 5%","PPS_6041",154.000000,-228.000000,90.000000,top
"C302","150nF PPS 5%","PPS_6041",154.000000,-244.000000,90.000000,top
"C312","100nF","C_0603_1608Metric",141.000000,-274.000000,90.000000,top
"C314","33pF C0G","C_0603_1608Metric",155.000000,-267.000000,90.000000,top
"C315","100nF","C_0603_1608Metric",141.000000,-264.000000,90.000000,top
"C316","100nF","C_0603_1608Metric",155.000000,-273.000000,90.000000,top
"C401","47nF C0G 5%","C_1206_3216Metric",186.000000,-228.000000,90.000000,top
"C402","47nF C0G 5%","C_1206_3216Metric",186.000000,-244.000000,90.000000,top
"C412","100nF","C_0603_1608Metric",173.000000,-274.000000,90.000000,top
"C414","33pF C0G","C_0603_1608Metric",187.000000,-267.000000,90.000000,top
"C415","100nF","C_0603_1608Metric",173.000000,-264.000000,90.000000,top
"C416","100nF","C_0603_1608Metric",187.000000,-273.000000,90.000000,top
"C501","10nF C0G 5%","C_1206_3216Metric",218.000000,-228.000000,90.000000,top
"C502","10nF C0G 5%","C_1206_3216Metric",218.000000,-244.000000,90.000000,top
"C512","100nF","C_0603_1608Metric",205.000000,-274.000000,90.000000,top
"C514","33pF C0G","C_0603_1608Metric",219.000000,-267.000000,90.000000,top
"C515","100nF","C_0603_1608Metric",205.000000,-264.000000,90.000000,top
"C516","100nF","C_0603_1608Metric",219.000000,-273.000000,90.000000,top
"CB11","100nF","C_0603_1608Metric",144.000000,-183.000000,90.000000,top
"CB12","100nF","C_0603_1608Metric",154.000000,-183.000000,90.000000,top
"CB21","100nF","C_0603_1608Metric",165.000000,-183.000000,90.000000,top
"CB22","100nF","C_0603_1608Metric",175.000000,-183.000000,90.000000,top
"CB31","100nF","C_0603_1608Metric",186.000000,-183.000000,90.000000,top
"CB32","100nF","C_0603_1608Metric",196.000000,-183.000000,90.000000,top
"CB41","100nF","C_0603_1608Metric",207.000000,-183.000000,90.000000,top
"CB42","100nF","C_0603_1608Metric",217.000000,-183.000000,90.000000,top
"CD11","100nF","C_0603_1608Metric",71.000000,-145.000000,90.000000,top
"CD12","10uF","C_0805_2012Metric",67.000000,-145.000000,90.000000,top
"CD13","100nF","C_0603_1608Metric",71.000000,-150.000000,90.000000,top
"CD14","10uF","C_0805_2012Metric",67.000000,-150.000000,90.000000,top
"CD15","100nF","C_0603_1608Metric",83.000000,-146.000000,90.000000,top
"CD16","10uF","C_0805_2012Metric",87.000000,-146.000000,90.000000,top
"CD17","2.2uF","C_0805_2012Metric",70.000000,-140.000000,0.000000,top
"CD18","2.2uF","C_0805_2012Metric",70.000000,-155.000000,0.000000,top
"CD19","100nF","C_0603_1608Metric",83.000000,-152.000000,90.000000,top
"CD21","100nF","C_0603_1608Metric",95.000000,-145.000000,90.000000,top
"CD22","10uF","C_0805_2012Metric",91.000000,-145.000000,90.000000,top
"CD23","100nF","C_0603_1608Metric",95.000000,-150.000000,90.000000,top
"CD24","10uF","C_0805_2012Metric",91.000000,-150.000000,90.000000,top
"CD25","100nF","C_0603_1608Metric",107.000000,-146.000000,90.000000,top
"CD26","10uF","C_0805_2012Metric",111.000000,-146.000000,90.000000,top
"CD27","2.2uF","C_0805_2012Metric",94.000000,-140.000000,0.000000,top
"CD28","2.2uF","C_0805_2012Metric",94.000000,-155.000000,0.000000,top
"CD29","100nF","C_0603_1608Metric",107.000000,-152.000000,90.000000,top
"CD31","100nF","C_0603_1608Metric",119.000000,-145.000000,90.000000,top
"CD32","10uF","C_0805_2012Metric",115.000000,-145.000000,90.000000,top
"CD33","100nF","C_0603_1608Metric",119.000000,-150.000000,90.000000,top
"CD34","10uF","C_0805_2012Metric",115.000000,-150.000000,90.000000,top
"CD35","100nF","C_0603_1608Metric",131.000000,-146.000000,90.000000,top
"CD36","10uF","C_0805_2012Metric",135.000000,-146.000000,90.000000,top
"CD37","2.2uF","C_0805_2012Metric",118.000000,-140.000000,0.000000,top
"CD38","2.2uF","C_0805_2012Metric",118.000000,-155.000000,0.000000,top
"CD39","100nF","C_0603_1608Metric",131.000000,-152.000000,90.000000,top
"CD110","2.2nF C0G","C_0603_1608Metric",72.000000,-163.000000,90.000000,top
"CD111","2.2nF C0G","C_0603_1608Metric",82.000000,-163.000000,90.000000,top
"CD210","2.2nF C0G","C_0603_1608Metric",96.000000,-163.000000,90.000000,top
"CD211","2.2nF C0G","C_0603_1608Metric",106.000000,-163.000000,90.000000,top
"CD310","2.2nF C0G","C_0603_1608Metric",120.000000,-163.000000,90.000000,top
"CD311","2.2nF C0G","C_0603_1608Metric",130.000000,-163.000000,90.000000,top
"CE11","2.2nF C0G","C_0603_1608Metric",85.000000,-206.000000,90.000000,top
"CE12","1nF C0G","C_0603_1608Metric",85.000000,-213.000000,90.000000,top
"CE13","1nF C0G","C_0603_1608Metric",135.000000,-85.480000,0.000000,top
"CE21","2.2nF C0G","C_0603_1608Metric",97.000000,-206.000000,90.000000,top
"CE22","1nF C0G","C_0603_1608Metric",97.000000,-213.000000,90.000000,top
"CE23","1nF C0G","C_0603_1608Metric",135.000000,-82.940000,0.000000,top
"CE31","2.2nF C0G","C_0603_1608Metric",109.000000,-206.000000,90.000000,top
"CE32","1nF C0G","C_0603_1608Metric",109.000000,-213.000000,90.000000,top
"CE33","1nF C0G","C_0603_1608Metric",135.000000,-80.400000,0.000000,top
"CE41","2.2nF C0G","C_0603_1608Metric",152.000000,-206.000000,90.000000,top
"CE42","1nF C0G","C_0603_1608Metric",152.000000,-213.000000,90.000000,top
"CE43","1nF C0G","C_0603_1608Metric",135.000000,-77.860000,0.000000,top
"CE51","2.2nF C0G","C_0603_1608Metric",164.000000,-206.000000,90.000000,top
"CE52","1nF C0G","C_0603_1608Metric",164.000000,-213.000000,90.000000,top
"CE53","1nF C0G","C_0603_1608Metric",135.000000,-75.320000,0.000000,top
"CE61","2.2nF C0G","C_0603_1608Metric",176.000000,-206.000000,90.000000,top
"CE62","1nF C0G","C_0603_1608Metric",176.000000,-213.000000,90.000000,top
"CE63","1nF C0G","C_0603_1608Metric",135.000000,-72.780000,0.000000,top
"CF101","220nF PPS 5%","PPS_6041",99.000000,-228.000000,90.000000,top
"CF102","220nF PPS 5%","PPS_6041",99.000000,-244.000000,90.000000,top
"CF111","30nF C0G 5%","C_1206_3216Metric",89.000000,-235.000000,0.000000,top
"CF112","30nF C0G 5%","C_1206_3216Metric",89.000000,-251.000000,0.000000,top
"CL1","10uF","C_0805_2012Metric",108.000000,-122.000000,90.000000,top
"CL2","10uF","C_0805_2012Metric",114.000000,-134.000000,90.000000,top
"CT1","100nF","C_0603_1608Metric",137.000000,-61.000000,90.000000,top
"CT2","10uF","C_0805_2012Metric",137.000000,-65.000000,90.000000,top
"CU1","100nF","C_0603_1608Metric",115.000000,-196.000000,90.000000,top
"CU2","100nF","C_0603_1608Metric",182.000000,-196.000000,90.000000,top
"CX1","100nF","C_0603_1608Metric",92.000000,-196.000000,90.000000,top
"CX2","100nF","C_0603_1608Metric",159.000000,-196.000000,90.000000,top
"DK1","1N4148W","D_SOD-123",228.000000,-312.000000,90.000000,top
"DK2","1N4148W","D_SOD-123",93.000000,-312.000000,90.000000,top
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
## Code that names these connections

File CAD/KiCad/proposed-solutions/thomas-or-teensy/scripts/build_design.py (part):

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    # Teensy top view, USB towards north; two separate 24-way sockets.
    left = ['GND']+list(map(str,range(13)))+['3V3']+list(map(str,range(24,33)))
    right = ['VIN','GND','3V3']+list(map(str,range(23,12,-1)))+['GND']+list(map(str,range(41,32,-1)))
    mapping={'GND':'GND','VIN':'TEENSY_VIN','3V3':'TEENSY_3V3','0':'link/to_teensy','1':'link/teensy_tx',
             '2':'DAC_XSMT','3':'MODE_TEENSY','7':'I2S_A_raw','32':'I2S_B_raw','9':'I2S_C_raw',
             '20':'LRCLK_raw','21':'BCLK_raw','22':'TEENSY_A8'}
    mapping.update({str(14+i):f'{b}/adc' for i,b in enumerate(BODY)})
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    for n,letter in enumerate('ABC'):
        sheet='dac_'+letter.lower()
        prefix=f'DAC_{letter}'
        pins={'1':'DAC_3V3','2':prefix+'/CAPP','3':'AGND','4':prefix+'/CAPM','5':prefix+'/VNEG',
              '6':BODY[n*2]+'/dac raw','7':BODY[n*2+1]+'/dac raw','8':'DAC_3V3','9':'AGND',
              '10':'AGND','11':'AGND','12':'AGND','13':'BCLK','14':'I2S_'+letter,'15':'LRCLK',
              '16':'AGND','17':'DAC_XSMT','18':prefix+'/LDOO','19':'AGND','20':'DAC_3V3'}
        names=dict(zip(map(str,range(1,21)),['CPVDD','CAPP','CPGND','CAPM','VNEG','OUTL','OUTR','AVDD','AGND','DEMP','FLT','SCK','BCK','DIN','LRCK','FMT','XSMT','LDOO','DGND','DVDD']))
        types={str(i):'power_in' if i in [1,3,8,9,19,20] else 'output' if i in [2,4,5,6,7] else 'power_out' if i==18 else 'input' for i in range(1,21)}
        add('UD'+str(n+1),'PCM5102APWR','Package_SO:TSSOP-20_4.4x6.5mm_P0.65mm',pins,sheet,
            '3-wire I2S; SCK/FMT/FLT/DEMP grounded. All ground pins use local AGND.',names,types,ds=DAC_DS)
        for supply in range(3):
            cap(f'CD{n+1}{supply*2+1}','100nF','DAC_3V3','AGND',sheet)
            cap(f'CD{n+1}{supply*2+2}','10uF','DAC_3V3','AGND',sheet,True)
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        cap(f'CU{chip+1}','100nF','TEENSY_3V3','AGND',sheet)
    # Mode is hardware-controlled. Relay 1/+ coil; pin8/-; common3,6; NC2,7; NO4,5.
    for n in range(3):
        pins={'1':'+5V','8':'COIL_LOW'}
        for j,(nc,common,no) in enumerate([(2,3,4),(7,6,5)]):
            i=2*n+j
            b=BODY[i]
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        resistor(f'RB{n}2','100K',b,'GND','logic')
        cap(f'CB{n}1','100nF',va,'GND','logic')
        cap(f'CB{n}2','100nF',vb,'GND','logic')
    parts['A1']['pins'].update(D18='link/mega_tx',D19='link/to_mega',D30='MODE_MEGA')
    parts['A1']['pin_types'].update(D18='output',D19='input',D30='input')
    for p in parts.values():
        p['uuid']=s.uid('component/'+p['ref'])
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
